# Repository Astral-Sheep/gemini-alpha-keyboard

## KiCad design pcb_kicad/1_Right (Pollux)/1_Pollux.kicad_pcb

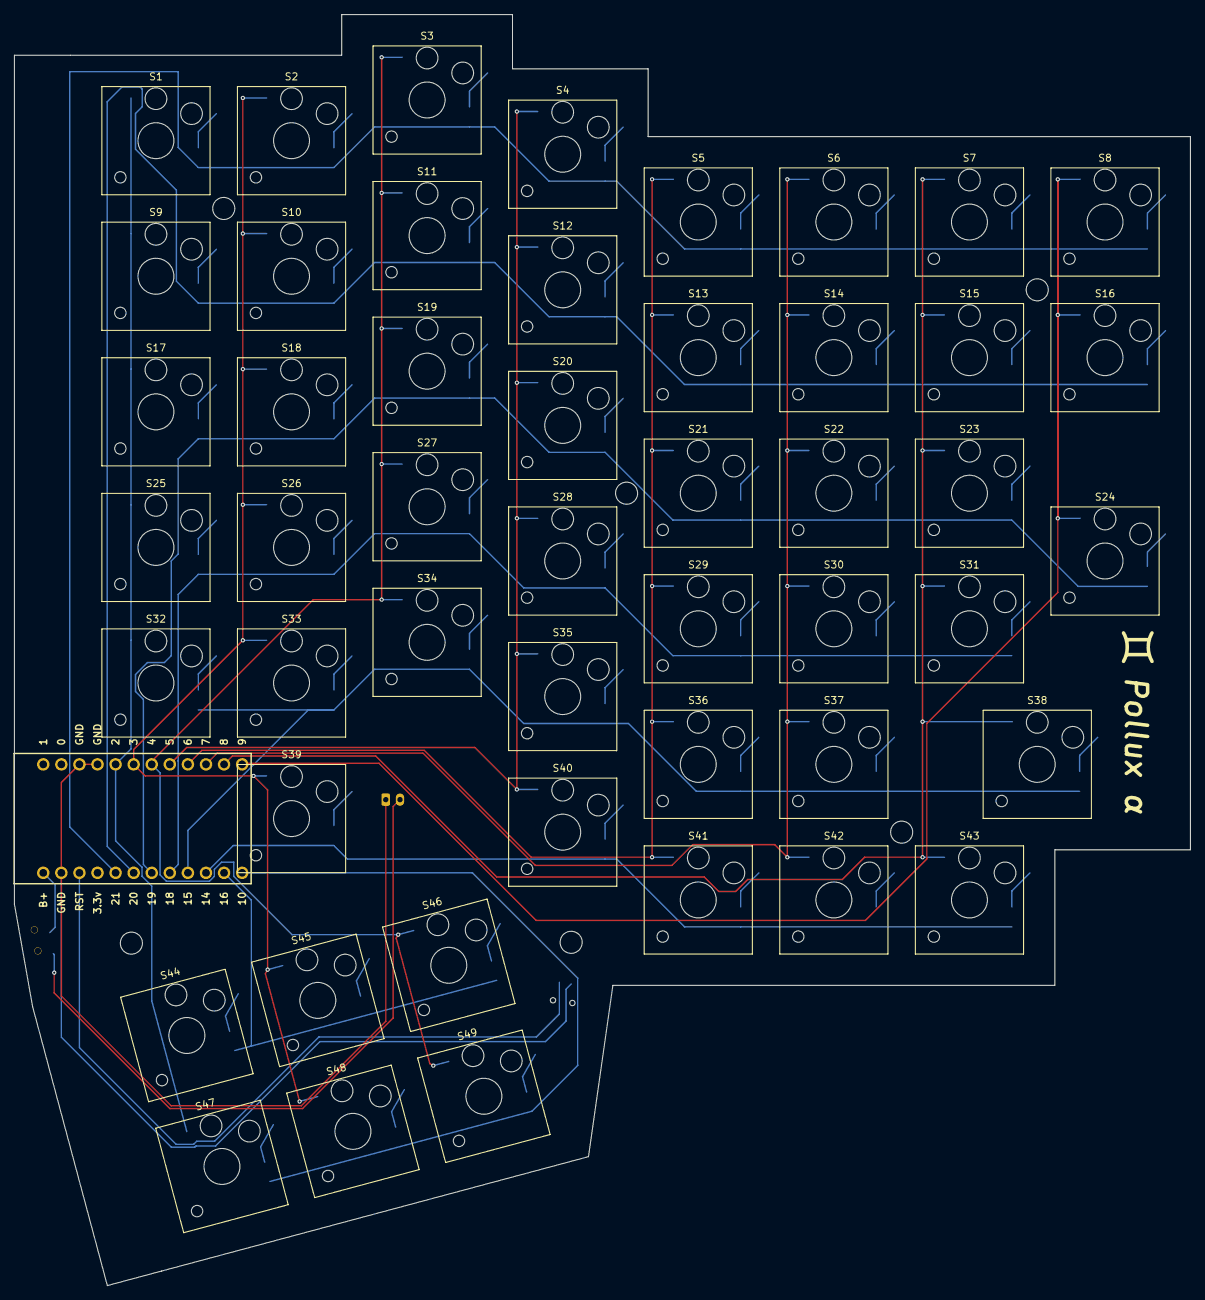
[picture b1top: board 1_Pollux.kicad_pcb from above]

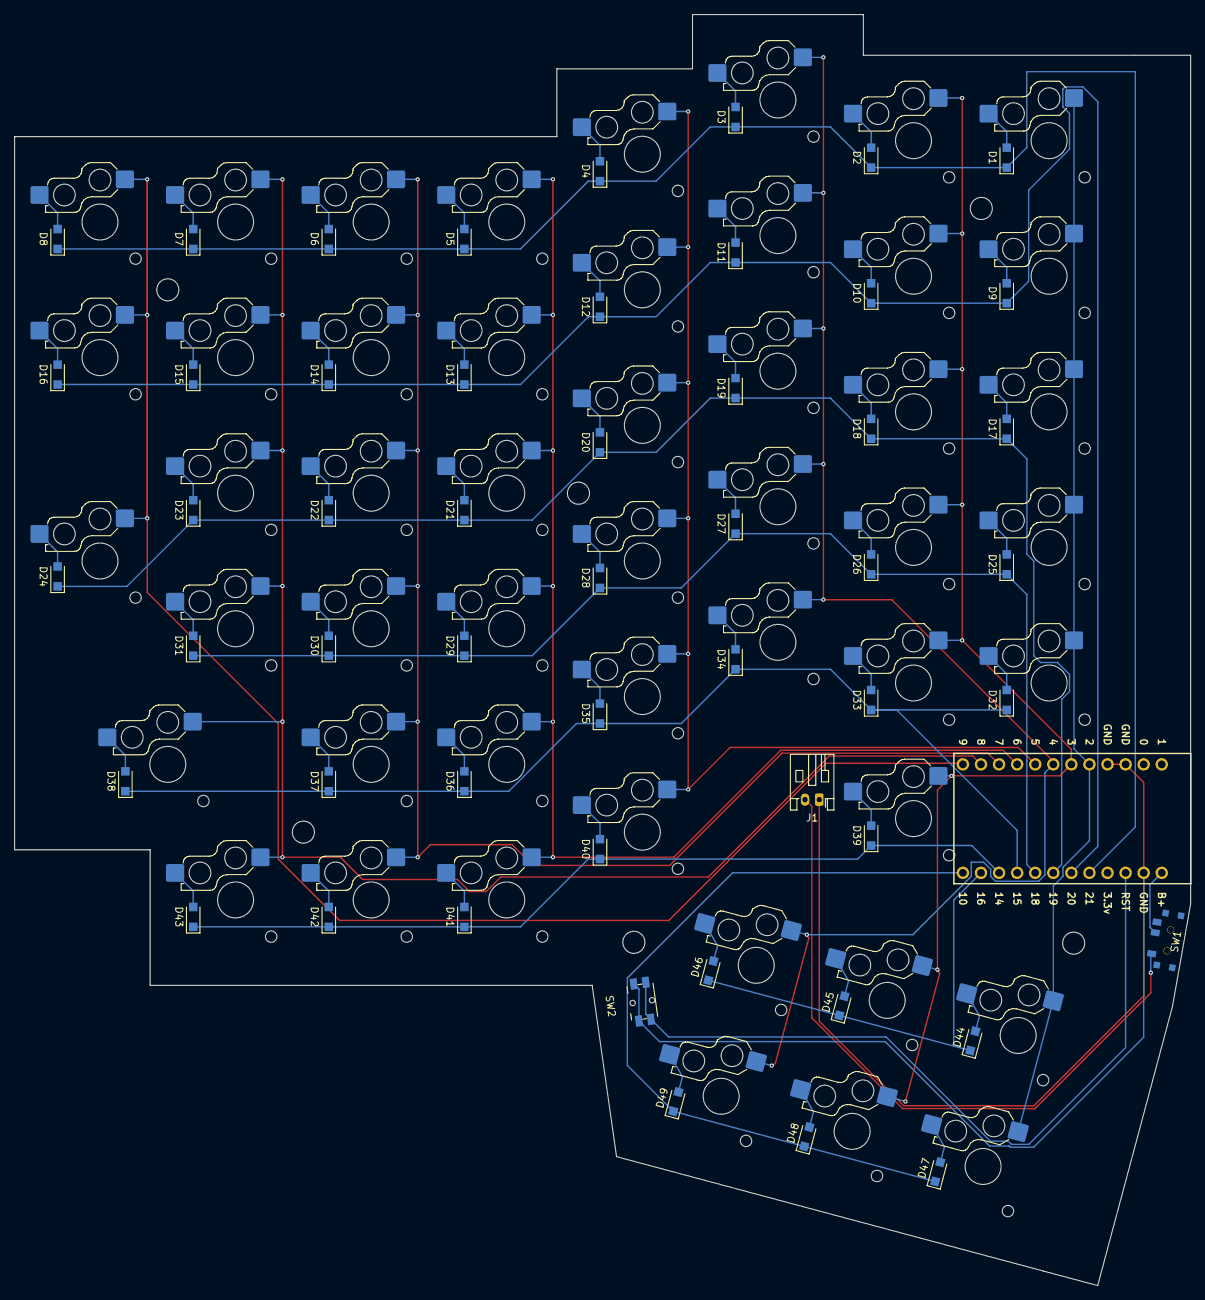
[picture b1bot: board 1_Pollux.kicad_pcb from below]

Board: 2 copper layers, 165.2 x 178.6 mm, 102 parts (53 on the bottom side), 69 nets.

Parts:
D1, D2, D3, D4, D5, D6, D7, D8, D9, D10, D11, D12, D13, D14, D15, D16, D17, D18, D19, D20, D21, D22, D23, D24, D25, D26, D27, D28, D29, D30, D31, D32, D33, D34, D35, D36, D37, D38, D39, D40, D41, D42, D43, D44, D45, D46, D47, D48, D49: Nexperia_CFP3_SOD-123W
J1: Conn_01x02; JST_PH_S2B-PH-K_1x02_P2.00mm_Horizontal
S1, S2, S3, S4, S5, S6, S7, S8, S9, S10, S11, S12, S13, S14, S15, S16, S17, S18, S19, S20, S21, S22, S23, S25, S26, S27, S28, S29, S30, S31, S32, S33, S34, S35, S36, S37, S40, S41, S42, S43, S44, S45, S46, S47, S48, S49: Hotswap_Choc_V2_1.00u
S24: Hotswap_Choc_V2_2.00u_90deg
S38: Hotswap_Choc_V2_2.00u
S39: Hotswap_Choc_V2_3.00u
SW1: Battery Switch; SPDT_C128955
SW2: Reset Switch; Panasonic_EVQPUL_EVQPUC
U1: Nice_Nano_V2

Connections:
+3.7V_{Battery}: SW1.2, U1.24 (B+)
/Column 0: S1.1, S9.1, S17.1, S25.1, S32.1, S44.1, S47.1, U1.5 (2)
/Column 1: S2.1, S10.1, S18.1, S26.1, S33.1, S39.1, S45.1, S48.1, U1.6 (3)
/Column 2: S3.1, S11.1, S19.1, S27.1, S34.1, S46.1, S49.1, U1.7 (4)
/Column 3: S4.1, S12.1, S20.1, S28.1, S35.1, S40.1, U1.8 (5)
/Column 4: S5.1, S13.1, S21.1, S29.1, S36.1, S41.1, U1.9 (6)
/Column 5: S6.1, S14.1, S22.1, S30.1, S37.1, S42.1, U1.10 (7)
/Column 6: S7.1, S15.1, S23.1, S31.1, S38.1, S43.1, U1.11 (8)
/Column 7: S8.1, S16.1, S24.1, U1.12 (9)
/POS: J1.2, SW1.1
/RST: SW2.2, U1.22 (RST)
/Row 0: D1.1 (K), D2.1 (K), D3.1 (K), D4.1 (K), D5.1 (K), D6.1 (K), D7.1 (K), D8.1 (K), U1.20 (21)
/Row 1: D9.1 (K), D10.1 (K), D11.1 (K), D12.1 (K), D13.1 (K), D14.1 (K), D15.1 (K), D16.1 (K), U1.19 (20)
/Row 2: D17.1 (K), D18.1 (K), D19.1 (K), D20.1 (K), D21.1 (K), D22.1 (K), D23.1 (K), D24.1 (K), U1.18 (19)
/Row 3: D25.1 (K), D26.1 (K), D27.1 (K), D28.1 (K), D29.1 (K), D30.1 (K), D31.1 (K), U1.17 (18)
/Row 4: D32.1 (K), D33.1 (K), D34.1 (K), D35.1 (K), D36.1 (K), D37.1 (K), D38.1 (K), U1.16 (15)
/Row 5: D39.1 (K), D40.1 (K), D41.1 (K), D42.1 (K), D43.1 (K), U1.15 (14)
/Row 6: D44.1 (K), D45.1 (K), D46.1 (K), U1.14 (16)
/Row 7: D47.1 (K), D48.1 (K), D49.1 (K), U1.13 (10)
GND: J1.1, SW2.1, U1.3 (GND), U1.4 (GND), U1.23 (GND)
unnamed: D1.2 (A), S1.2
unnamed: D2.2 (A), S2.2
unnamed: D3.2 (A), S3.2
unnamed: D4.2 (A), S4.2
unnamed: D5.2 (A), S5.2
unnamed: D6.2 (A), S6.2
unnamed: D7.2 (A), S7.2
unnamed: D8.2 (A), S8.2
unnamed: D9.2 (A), S9.2
unnamed: D10.2 (A), S10.2
unnamed: D11.2 (A), S11.2
unnamed: D12.2 (A), S12.2
unnamed: D13.2 (A), S13.2
unnamed: D14.2 (A), S14.2
unnamed: D15.2 (A), S15.2
unnamed: D16.2 (A), S16.2
unnamed: D17.2 (A), S17.2
unnamed: D18.2 (A), S18.2
unnamed: D19.2 (A), S19.2
unnamed: D20.2 (A), S20.2
unnamed: D21.2 (A), S21.2
unnamed: D22.2 (A), S22.2
unnamed: D23.2 (A), S23.2
unnamed: D24.2 (A), S24.2
unnamed: D25.2 (A), S25.2
unnamed: D26.2 (A), S26.2
unnamed: D27.2 (A), S27.2
unnamed: D28.2 (A), S28.2
unnamed: D29.2 (A), S29.2
unnamed: D30.2 (A), S30.2
unnamed: D31.2 (A), S31.2
unnamed: D32.2 (A), S32.2
unnamed: D33.2 (A), S33.2
unnamed: D34.2 (A), S34.2
unnamed: D35.2 (A), S35.2
unnamed: D36.2 (A), S36.2
unnamed: D37.2 (A), S37.2
unnamed: D38.2 (A), S38.2
unnamed: D39.2 (A), S39.2
unnamed: D40.2 (A), S40.2
unnamed: D41.2 (A), S41.2
unnamed: D42.2 (A), S42.2
unnamed: D43.2 (A), S43.2
unnamed: D44.2 (A), S44.2
unnamed: D45.2 (A), S45.2
unnamed: D46.2 (A), S46.2
unnamed: D47.2 (A), S47.2
unnamed: D48.2 (A), S48.2
unnamed: D49.2 (A), S49.2
